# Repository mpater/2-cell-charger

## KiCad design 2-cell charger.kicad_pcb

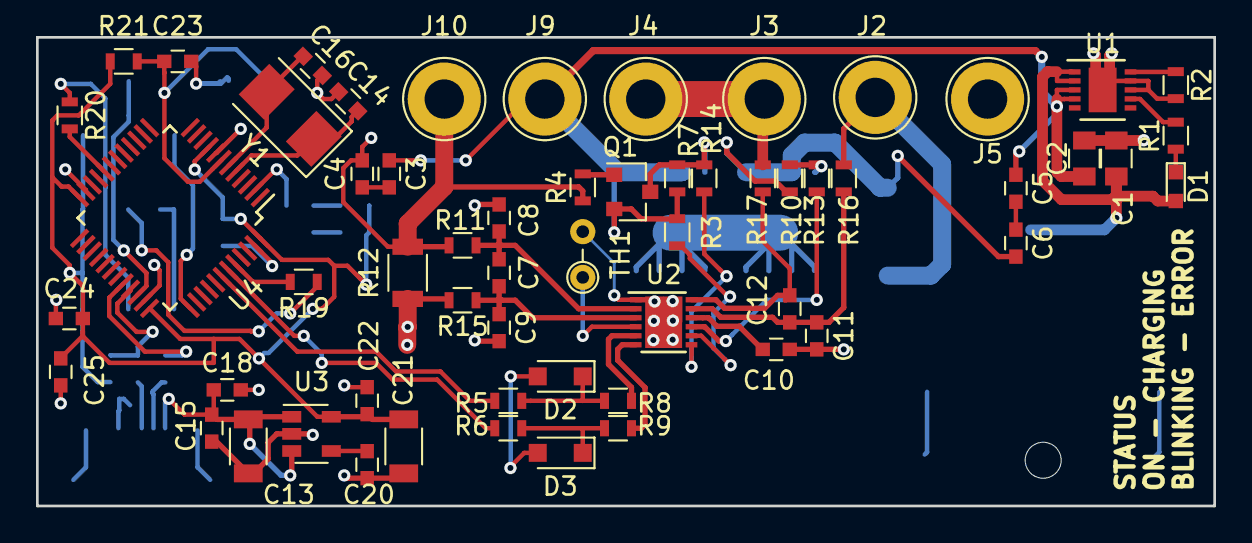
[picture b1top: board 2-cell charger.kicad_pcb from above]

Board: 2 copper layers, 65.4 x 26.0 mm, 75 parts (0 on the bottom side), 50 nets.

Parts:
C1, C2: 4.7uF; C_0805
C3, C4, C5, C6, C7, C8, C9, C11, C12, C15, C18, C20, C22, C23, C24, C25, C26: 0.1uF; C_0603
C10: 2.2uF; C_0603
C13, C21: 10uF; C_1206
C14, C16: 12pF; C_0603
D1: RED_LED; LED_0603
D2, D3: MM3Z5V6C; D_SOD-323_HandSoldering
D4, D5: LED_ALT; LED_0603
F1: Polyfuse; R_1812
J1: BARREL_JACK; BARREL_JACK_SMD
J2: 2s POS; 1pin
J3: 2s NEG; 1pin
J4: 1s POS; 1pin
J5: 1s NEG; 1pin
J6: USB_OTG; USB_Micro-B
J7: CONN_01X04; Pin_Header_Straight_1x04_Pitch2.54mm_SMD_Pin1Right
J8: CONN_02X03; Pin_Header_Straight_2x03_Pitch2.54mm_SMD
J9: PACK POS; 1pin
J10: PACK NEG; 1pin
Q1: 2N7002K; SOT-23
Q2, Q3: Q_NMOS_DGS; SO-8_PowerPAK
R1: 1k; R_0603
R2: 1.15k; R_0603
R3: 10; R_0603
R4, R21, R22: 10k; R_0603
R5, R6, R8, R9, R11, R15, R16: 100; R_0603
R7, R10: 10M; R_0603
R12: 3m; R_1206
R13, R14: 5.1k; R_0603
R17: 5; R_0603
R18, R25: 510; R_0603
R19, R20: 100k; R_0603
R23, R24: 22; R_0603
SW1: SW_Push; SW_SPST_EVQPE1
TH1: NTC10k; R_Axial_DIN0204_L3.6mm_D1.6mm_P2.54mm_Vertical
U1: MCP73223; DFN-10-1EP_3x3mm_Pitch0.5mm
U2: BQ28Z610; DFN-12-1EP_3x3mm_Pitch0.5mm
U3: AP131-33; SOT-23-5
U4: STM32F103C8Tx; LQFP-48_7x7mm_Pitch0.5mm
Y1: 8M0; Crystal_SMD_5032-2pin_5.0x3.2mm

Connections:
+3V3: C21.1, C22.1, C24.1, C25.1, C26.1, D4.2, D5.2, J7.1, J8.1, J8.2, R21.1, R22.1, U3.5, U4.9, U4.24, U4.36, U4.48
+5V: C13.1, C15.1, C18.1, J6.1, U3.1, U3.3
/MCU and USB/BOOT0: J8.3, R19.1
/MCU and USB/BOOT1: J8.4, R20.1
/MCU and USB/C13: R25.2, U4.2
/MCU and USB/RESET: C23.1, R21.2, SW1.1, U4.7
/MCU and USB/SWCLK: J7.3, U4.37
/MCU and USB/SWDIO: J7.2, U4.34
/MCU and USB/USB_DM: J6.2, R23.2
/MCU and USB/USB_DP: J6.3, R24.2
GND: C8.2, C9.2, C10.2, C11.2, J5.1, R12.2, R15.2, TH1.2, U2.1, U2.13
unnamed: C1.1, D1.2, J1.1, U1.1, U1.2
unnamed: C3.2, C4.1
unnamed: C5.2, C6.1
unnamed: C6.2, F1.2, Q3.3, R10.2
unnamed: C7.1, C9.1, R15.1, U2.3
unnamed: C7.2, C8.1, R11.1, U2.2
unnamed: C10.1, U2.10
unnamed: C11.1, C12.1, R16.1, U2.11
unnamed: C12.2, R17.1, U2.12
unnamed: C14.1, U4.5, Y1.1
unnamed: C16.1, U4.6, Y1.2
unnamed: C20.1, U3.4
unnamed: D1.1, R1.1
unnamed: D2.1, R5.2, R8.1
unnamed: D3.1, R6.2, R9.1
unnamed: D4.1, R18.1
unnamed: D5.1, R25.1
unnamed: F1.1, J2.1, R16.2
unnamed: J3.1, J4.1, R17.2
unnamed: Q1.1, R4.2
unnamed: Q1.3, Q2.2, R7.1, R14.1
unnamed: Q2.1, Q3.1
unnamed: Q3.2, R10.1, R13.1
unnamed: R1.2, U1.7
unnamed: R2.1, U1.10
unnamed: R3.1, U2.8
unnamed: R8.2, U2.5
unnamed: R9.2, U2.6
unnamed: R13.2, U2.9
unnamed: R14.2, U2.7
unnamed: R19.2, U4.44
unnamed: R20.2, U4.20
unnamed: R22.2, R24.1, U4.33
unnamed: R23.1, U4.32
unnamed: TH1.1, U2.4
PACK_NEG: C1.2, C2.2, C4.2, C13.2, C14.2, C15.2, C16.2, C18.2, C20.2, C21.2, C22.2, C23.2, C24.2, C25.2, C26.2, D2.2, D3.2, J1.2, J1.3, J6.5, J6.6, J7.4, J8.5, J8.6, J10.1, R2.2, R4.1, R11.2, R12.1, R18.2, SW1.2, U1.8, U1.9, U1.11, U3.2, U4.8, U4.23, U4.35, U4.47
PACK_POS: C2.1, C3.1, C5.1, J9.1, Q1.2, Q2.3, R3.2, R7.2, U1.3, U1.4
SCA: R6.1, U4.43
SCL: R5.1, U4.42
